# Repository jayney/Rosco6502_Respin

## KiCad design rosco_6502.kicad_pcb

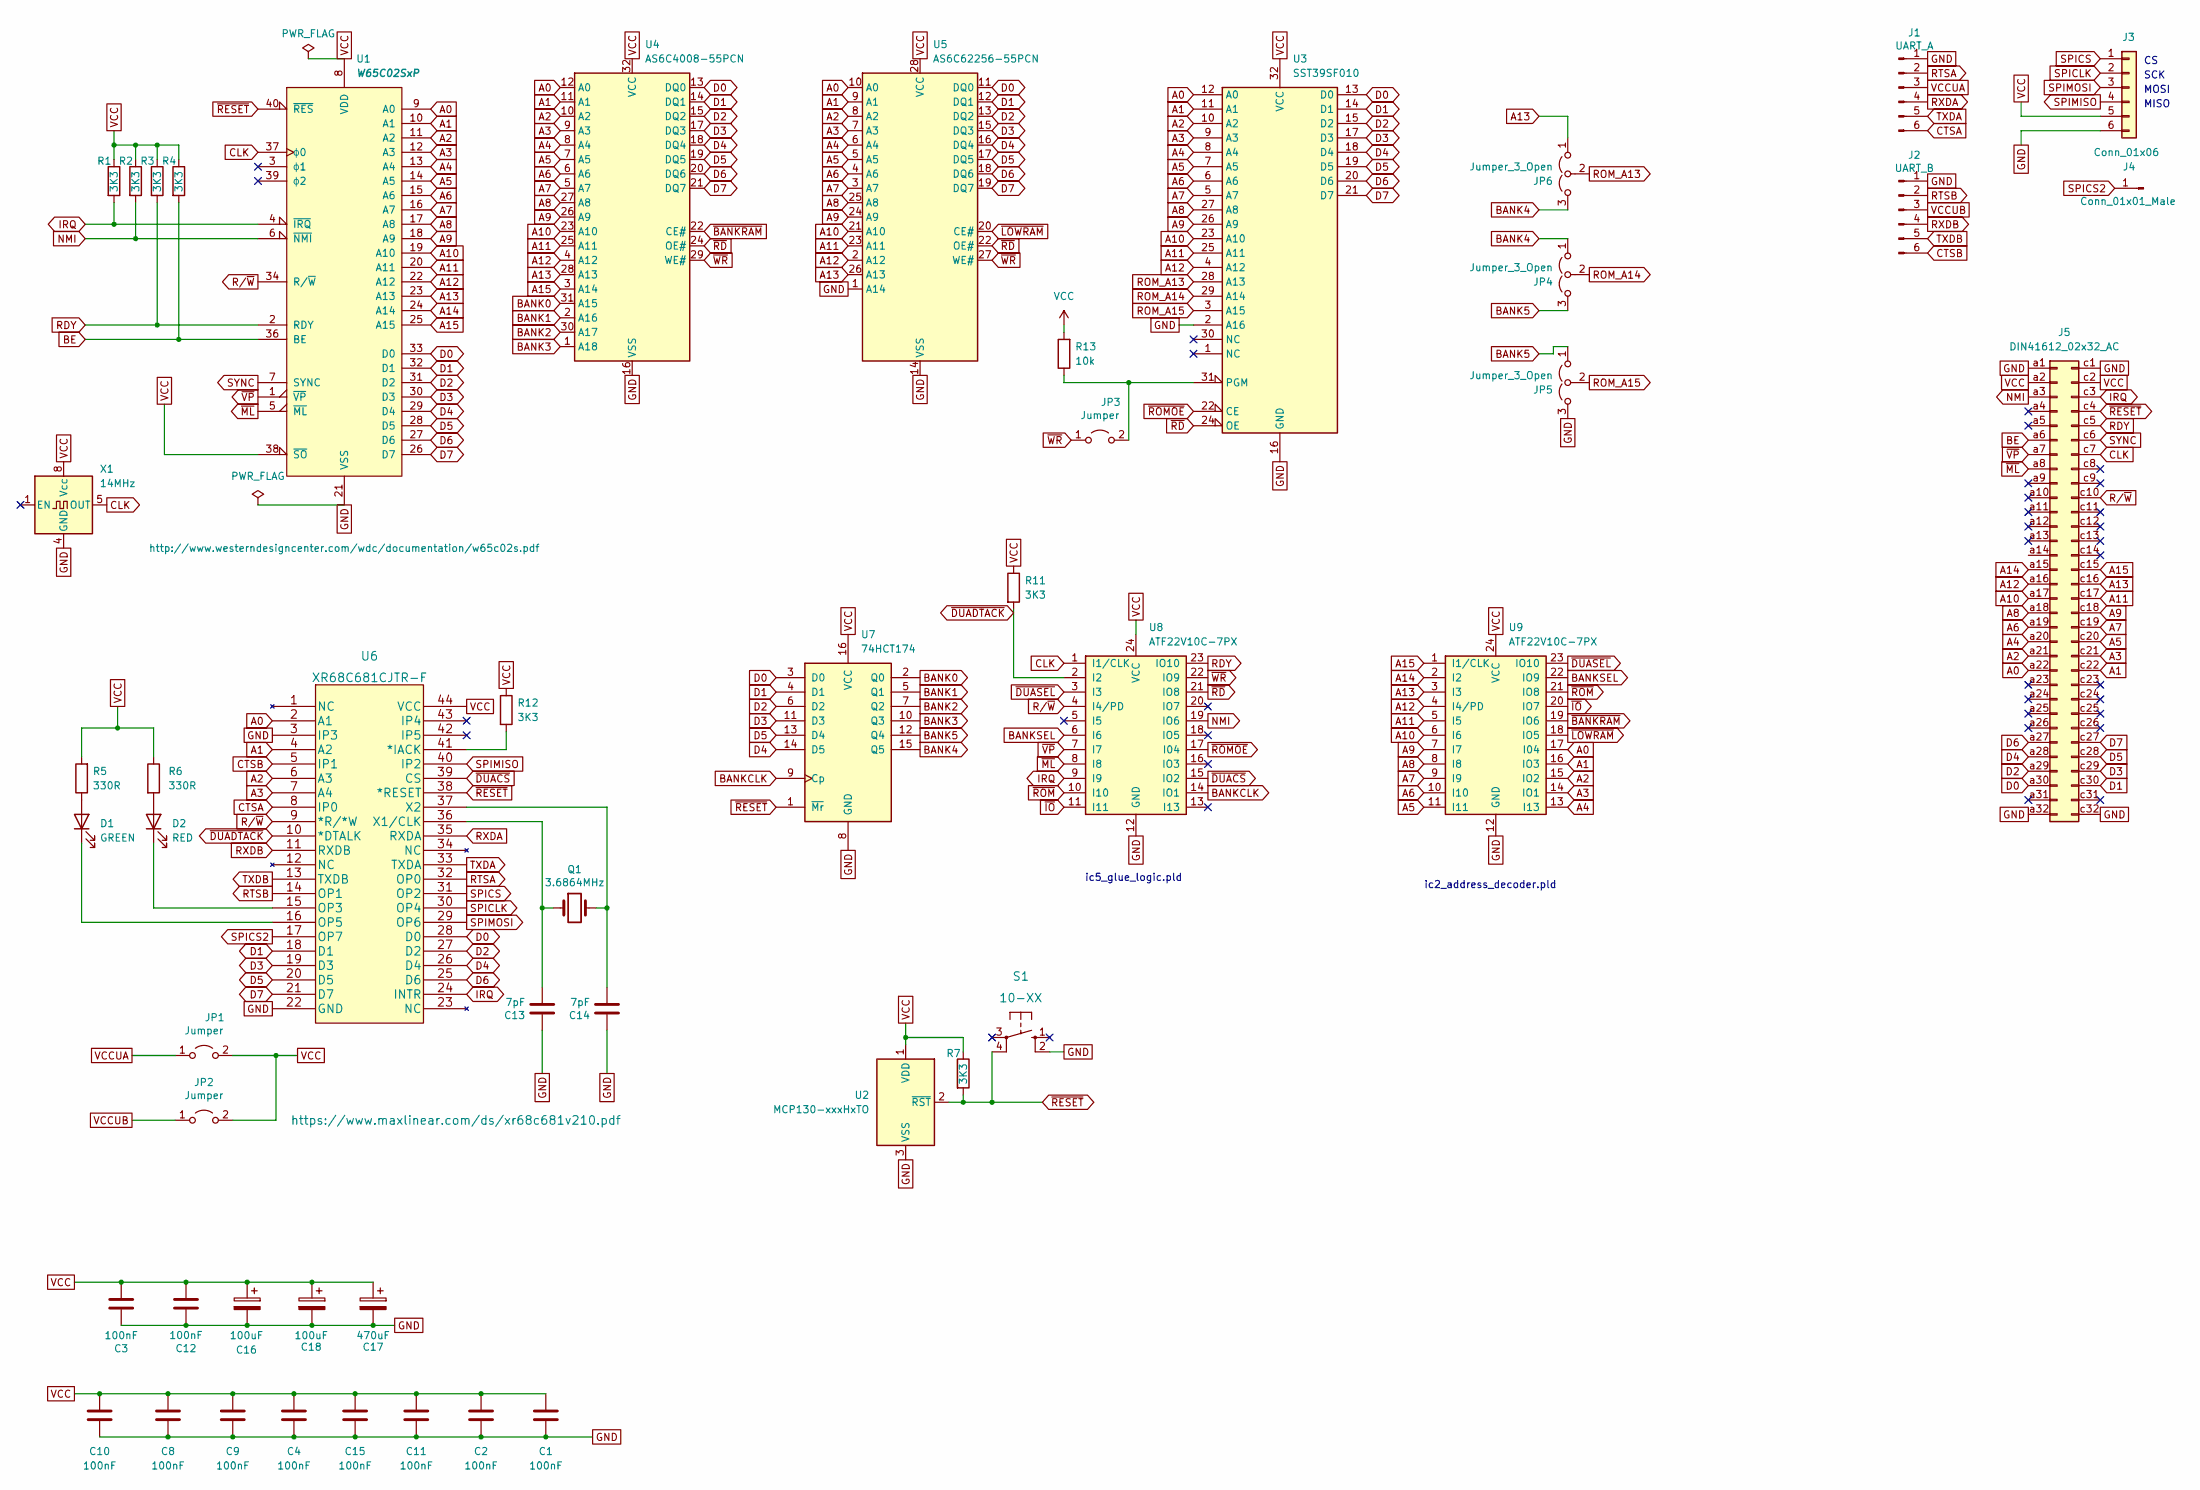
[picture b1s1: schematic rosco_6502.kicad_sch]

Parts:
C1, C2, C3, C4, C8, C9, C10, C11, C12, C15: 100nF; C_Disc_D3.0mm_W1.6mm_P2.50mm; LCSC C14663
C13, C14: 7pF; C_Disc_D3.0mm_W1.6mm_P2.50mm; LCSC C1682
C16, C18: 100uF; CP_Radial_D6.3mm_P2.50mm
C17: 470uF; CP_Radial_D7.5mm_P2.50mm
D1: GREEN; LED_D3.0mm
D2: RED; LED_D3.0mm
J1: UART_A; PinHeader_1x06_P2.54mm_Vertical
J2: UART_B; PinHeader_1x06_P2.54mm_Vertical
J3: Conn_01x06; PinHeader_1x06_P2.54mm_Vertical
J4: Conn_01x01_Male; PinHeader_1x01_P2.54mm_Vertical
J5: DIN41612_02x32_AC; DIN41612_C_2x32_Male_Horizontal_THT
JP1, JP2, JP3: Jumper; PinHeader_1x02_P2.54mm_Vertical
JP4, JP5, JP6: Jumper_3_Open; SolderJumper-3_P1.3mm_Open_RoundedPad1.0x1.5mm_NumberLabels
Q1: 3.6864MHz; Crystal_HC49-4H_Vertical
R1, R2, R3, R4, R11, R12: 3K3; R_Axial_DIN0204_L3.6mm_D1.6mm_P7.62mm_Horizontal; LCSC C22978
R5, R6: 330R; R_Axial_DIN0204_L3.6mm_D1.6mm_P7.62mm_Horizontal; LCSC C23138
R7: 3K3; R_Axial_DIN0204_L3.6mm_D1.6mm_P7.62mm_Horizontal
R13: 10k; R_Axial_DIN0204_L3.6mm_D1.6mm_P7.62mm_Horizontal; LCSC C25804
S1: 10-XX; B3F-10XX
U1: W65C02SxP; DIP-40_W15.24mm_Socket_LongPads
U2: MCP130-xxxHxTO; TO-92_Inline
U3: SST39SF010; DIP-32_W15.24mm_Socket_LongPads
U4: AS6C4008-55PCN; DIP-32_W15.24mm_Socket_LongPads
U5: AS6C62256-55PCN; DIP-28_W15.24mm_Socket_LongPads
U6: XR68C681CJTR-F; PLCC-44_THT-Socket
U7: 74HCT174; DIP-16_W7.62mm_Socket_LongPads
U8, U9: ATF22V10C-7PX; DIP-24_W7.62mm_Socket_LongPads
X1: 14MHz; Oscillator_DIP-8

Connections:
A0: J5.a22, U1.9 (A0), U3.12 (A0), U4.12 (A0), U5.10 (A0), U6.2 (A1), U9.17 (I04)
A1: J5.c22, U1.10 (A1), U3.11 (A1), U4.11 (A1), U5.9 (A1), U6.4 (A2), U9.16 (IO3)
A2: J5.a21, U1.11 (A2), U3.10 (A2), U4.10 (A2), U5.8 (A2), U6.6 (A3), U9.15 (IO2)
A3: J5.c21, U1.12 (A3), U3.9 (A3), U4.9 (A3), U5.7 (A3), U6.7 (A4), U9.14 (IO1)
A4: J5.a20, U1.13 (A4), U3.8 (A4), U4.8 (A4), U5.6 (A4), U9.13 (I13)
A5: J5.c20, U1.14 (A5), U3.7 (A5), U4.7 (A5), U5.5 (A5), U9.11 (I11)
A6: J5.a19, U1.15 (A6), U3.6 (A6), U4.6 (A6), U5.4 (A6), U9.10 (I10)
A7: J5.c19, U1.16 (A7), U3.5 (A7), U4.5 (A7), U5.3 (A7), U9.9 (I9)
A8: J5.a18, U1.17 (A8), U3.27 (A8), U4.27 (A8), U5.25 (A8), U9.8 (I8)
A9: J5.c18, U1.18 (A9), U3.26 (A9), U4.26 (A9), U5.24 (A9), U9.7 (I7)
A10: J5.a17, U1.19 (A10), U3.23 (A10), U4.23 (A10), U5.21 (A10), U9.6 (I6)
A11: J5.c17, U1.20 (A11), U3.25 (A11), U4.25 (A11), U5.23 (A11), U9.5 (I5)
A12: J5.a16, U1.22 (A12), U3.4 (A12), U4.4 (A12), U5.2 (A12), U9.4 (I4/PD)
A13: J5.c16, JP6.1 (A), U1.23 (A13), U4.28 (A13), U5.26 (A13), U9.3 (I3)
A14: J5.a15, U1.24 (A14), U9.2 (I2)
A15: J5.c15, U1.25 (A15), U4.3 (A14), U9.1 (I1/CLK)
BANK0: U4.31 (A15), U7.2 (Q0)
BANK1: U4.2 (A16), U7.5 (Q1)
BANK2: U4.30 (A17), U7.7 (Q2)
BANK3: U4.1 (A18), U7.10 (Q3)
BANK4: JP4.1 (A), JP6.3 (B), U7.15 (Q5)
BANK5: JP4.3 (B), JP5.1 (A), U7.12 (Q4)
BANKCLK: U7.9 (Cp), U8.14 (IO1)
BANKSEL: U8.6 (I6), U9.22 (IO9)
BE: J5.a6, R4.2, U1.36 (BE)
CLK: J5.c7, U1.37 (ϕ0), U8.1 (I1/CLK), X1.5 (OUT)
CTSA: J1.6, U6.8 (IP0)
CTSB: J2.6, U6.5 (IP1)
D0: J5.a30, U1.33 (D0), U3.13 (D0), U4.13 (DQ0), U5.11 (DQ0), U6.28 (D0), U7.3 (D0)
D1: J5.c30, U1.32 (D1), U3.14 (D1), U4.14 (DQ1), U5.12 (DQ1), U6.18 (D1), U7.4 (D1)
D2: J5.a29, U1.31 (D2), U3.15 (D2), U4.15 (DQ2), U5.13 (DQ2), U6.27 (D2), U7.6 (D2)
D3: J5.c29, U1.30 (D3), U3.17 (D3), U4.17 (DQ3), U5.15 (DQ3), U6.19 (D3), U7.11 (D3)
D4: J5.a28, U1.29 (D4), U3.18 (D4), U4.18 (DQ4), U5.16 (DQ4), U6.26 (D4), U7.14 (D5)
D5: J5.c28, U1.28 (D5), U3.19 (D5), U4.19 (DQ5), U5.17 (DQ5), U6.20 (D5), U7.13 (D4)
D6: J5.a27, U1.27 (D6), U3.20 (D6), U4.20 (DQ6), U5.18 (DQ6), U6.25 (D6)
D7: J5.c27, U1.26 (D7), U3.21 (D7), U4.21 (DQ7), U5.19 (DQ7), U6.21 (D7)
GND: C1.1, C2.1, C3.1, C4.1, C8.1, C9.1, C10.1, C11.1, C12.1, C13.1, C14.1, C15.1, C16.2, C17.2, C18.2, J1.1, J2.1, J3.6, J5.a1, J5.a32, J5.c1, J5.c32, JP5.3 (B), S1.2 (S1), U1.21 (VSS), U2.3 (VSS), U3.2 (A16), U3.16 (GND), U4.16 (VSS), U5.1 (A14), U5.14 (VSS), U6.3 (IP3), U6.22 (GND), U7.8 (GND), U8.12 (GND), U9.12 (GND), X1.4 (GND)
IRQ: J5.c3, R1.2, U1.4 (~IRQ), U6.24 (INTR), U8.9 (I9)
NMI: J5.a3, R2.2, U1.6 (~NMI), U8.19 (IO6)
unnamed: D1.2 (A), R5.1
unnamed: D1.1 (K), U6.16 (OP5)
unnamed: D2.2 (A), R6.2
unnamed: D2.1 (K), U6.15 (OP3)
unnamed: JP3.2 (B), R13.1, U3.31 (PGM)
unnamed: R12.2, U6.41 (*IACK)
unnamed: C13.2, Q1.1, U6.36 (X1/CLK)
unnamed: C14.2, Q1.2, U6.37 (X2)
RDY: J5.c5, R3.2, U1.2 (RDY), U8.23 (IO10)
ROM_A13: JP6.2 (C), U3.28 (A13)
ROM_A14: JP4.2 (C), U3.29 (A14)
ROM_A15: JP5.2 (C), U3.3 (A15)
RTSA: J1.2, U6.32 (OP0)
RTSB: J2.2, U6.14 (OP1)
RXDA: J1.4, U6.35 (RXDA)
RXDB: J2.4, U6.11 (RXDB)
R/~W: J5.c10, U1.34 (R/~W), U6.9 (*R/*W), U8.4 (I4/PD)
SPICLK: J3.2, U6.30 (OP4)
SPICS: J3.1, U6.31 (OP2)
SPICS2: J4.1, U6.17 (OP7)
SPIMISO: J3.4, U6.40 (IP2)
SPIMOSI: J3.3, U6.29 (OP6)
SYNC: J5.c6, U1.7 (SYNC)
TXDA: J1.5, U6.33 (TXDA)
TXDB: J2.5, U6.13 (TXDB)
VCC: C1.2, C2.2, C3.2, C4.2, C8.2, C9.2, C10.2, C11.2, C12.2, C15.2, C16.1, C17.1, C18.1, J3.5, J5.a2, J5.c2, JP1.2 (B), JP2.2 (B), R1.1, R2.1, R3.1, R4.1, R5.2, R6.1, R7.1, R11.1, R12.1, R13.2, U1.8 (VDD), U1.38 (~SO), U2.1 (VDD), U3.32 (VCC), U4.32 (VCC), U5.28 (VCC), U6.44 (VCC), U7.16 (VCC), U8.24 (VCC), U9.24 (VCC), X1.8 (Vcc)
VCCUA: J1.3, JP1.1 (A)
VCCUB: J2.3, JP2.1 (A)
~BANKRAM: U4.22 (CE#), U9.19 (IO6)
~DUACS: U6.39 (CS), U8.15 (IO2)
~DUADTACK: R11.2, U6.10 (*DTALK), U8.2 (I2)
~DUASEL: U8.3 (I3), U9.23 (IO10)
~IO: U8.11 (I11), U9.20 (IO7)
~LOWRAM: U5.20 (CE#), U9.18 (IO5)
~ML: J5.a8, U1.5 (~ML), U8.8 (I8)
~RD: U3.24 (OE), U4.24 (OE#), U5.22 (OE#), U8.21 (IO8)
~RESET: J5.c4, R7.2, S1.4 (P1), U1.40 (~RES), U2.2 (~RST), U6.38 (*RESET), U7.1 (~Mr)
~ROMOE: U3.22 (CE), U8.17 (I04)
~ROM: U8.10 (I10), U9.21 (IO8)
~VP: J5.a7, U1.1 (~VP), U8.7 (I7)
~WR: JP3.1 (A), U4.29 (WE#), U5.27 (WE#), U8.22 (IO9)

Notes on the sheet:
ic5_glue_logic.pld
SCK
ic2_address_decoder.pld
MOSI
MISO

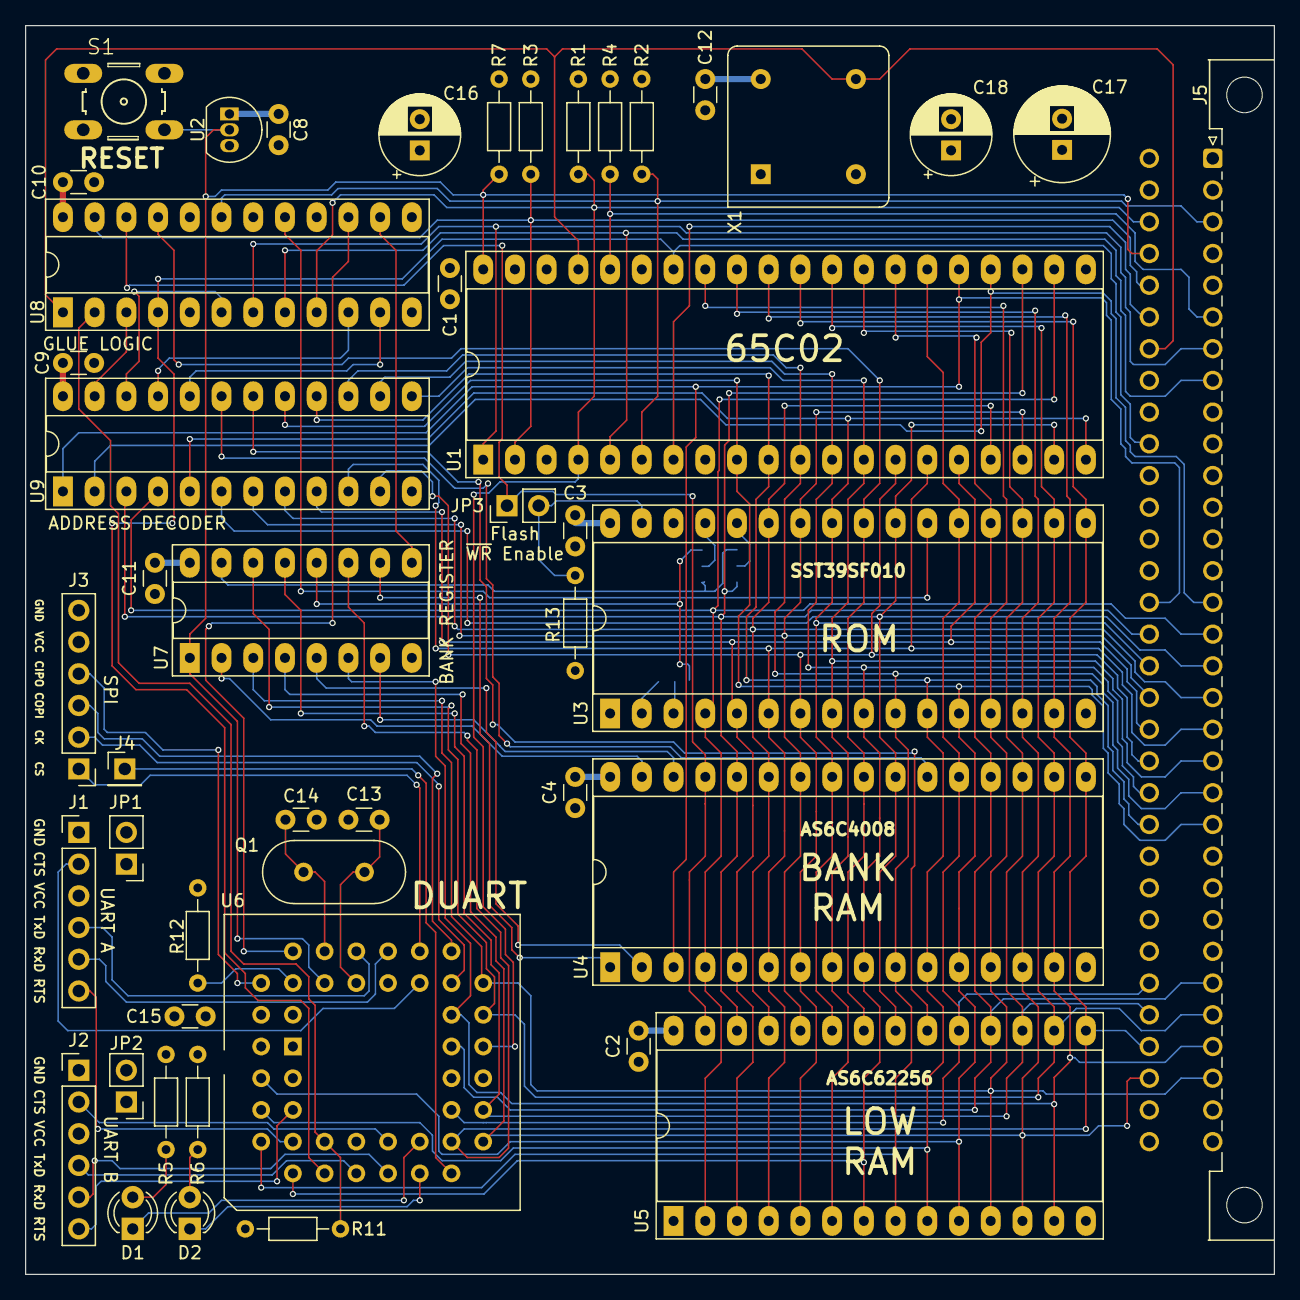
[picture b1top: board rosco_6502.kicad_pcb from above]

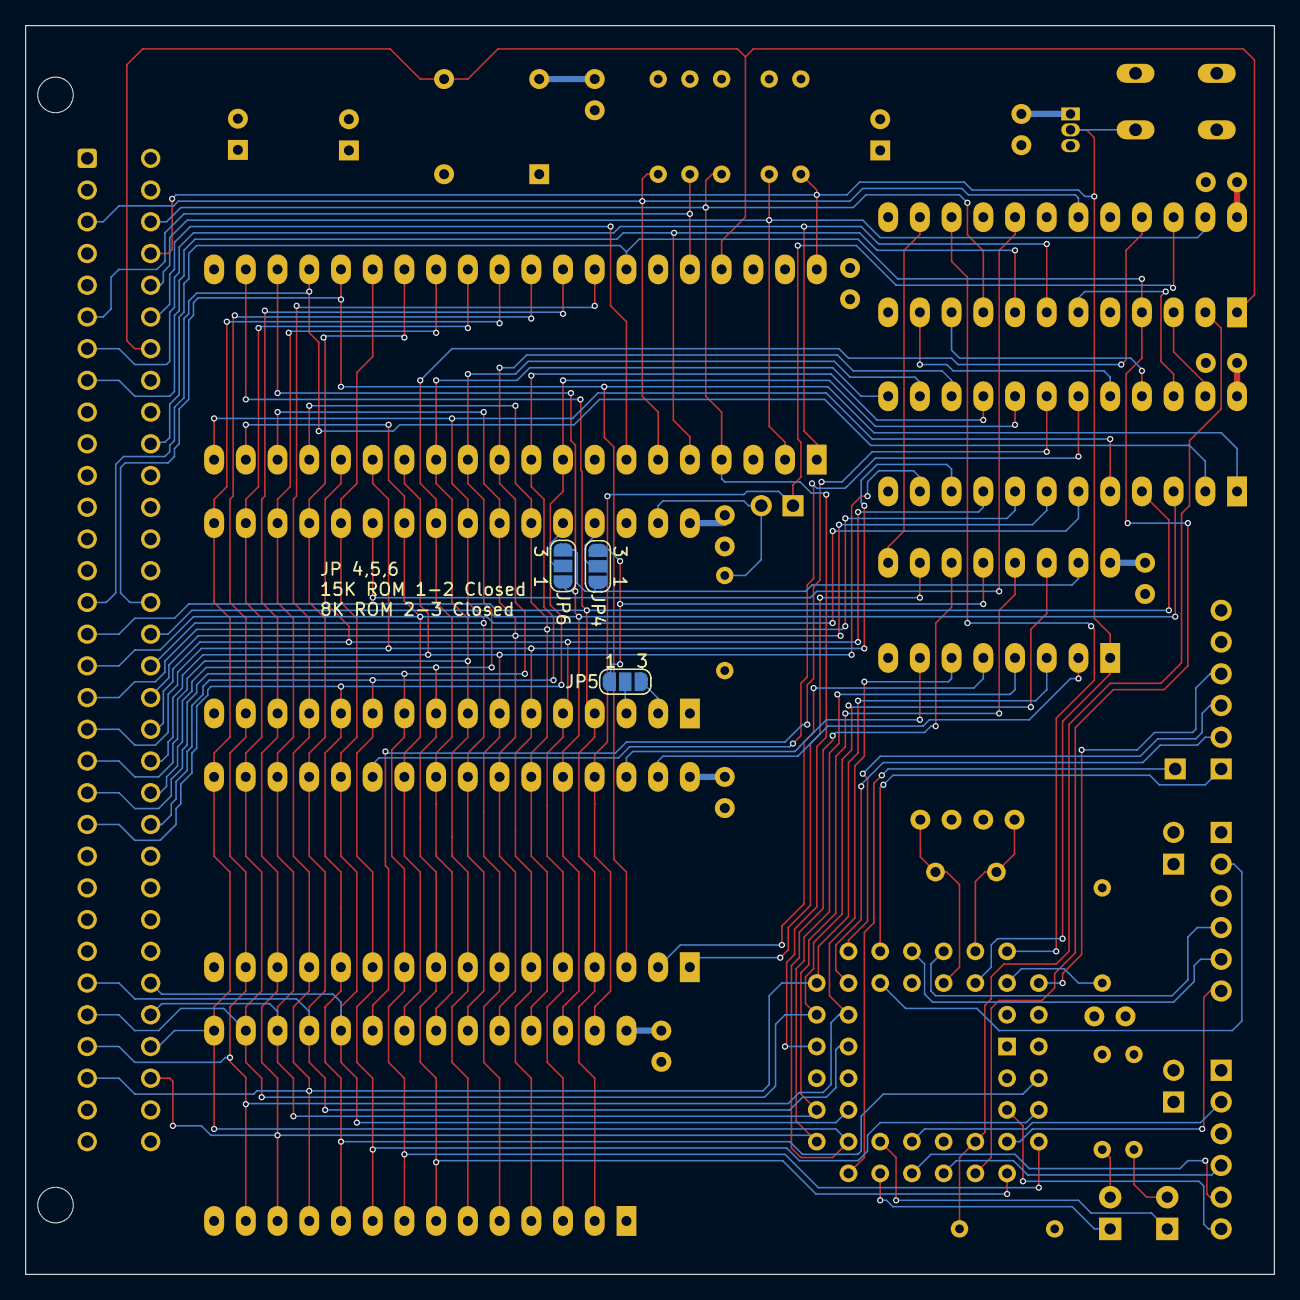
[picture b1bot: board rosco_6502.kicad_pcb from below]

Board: 4 copper layers, 100.0 x 100.0 mm, 50 parts (3 on the bottom side), 80 nets.

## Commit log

2024-05-22 Update for new DUART select logic
    And some tidying up
2024-05-22 SMD components replaced with THT

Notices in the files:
rosco_6502.kicad_pcb:
Copyright (c)2022-2023 Ross Bamford & Contributors
Open Source Hardware (CERN OHL)
